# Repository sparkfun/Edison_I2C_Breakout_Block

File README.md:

SparkFun Edison I2C Breakout Block
==================================

[*SparkFun Edison I2C Breakout Block(DEV-13034)*](https://www.sparkfun.com/products/13034)

This I2C Block simply breaks out an I2C bus on the Intel® Edison while level shifting it from 1.8V to your sensors voltage. This a simple board that can snap into your Edison and be used right away.

Repository Contents
-------------------
* **Hardware** - All Eagle diesgn files (.brd, .sch)
* **/Production** - Test bed files and production panel files

License Information
-------------------
The hardware is released under [Creative Commons ShareAlike 4.0 International](https://creativecommons.org/licenses/by-sa/4.0/).
The code is beerware; if you see me (or any other SparkFun employee) at the local, and you've found our code helpful, please buy us a round!

Distributed as-is; no warranty is given.

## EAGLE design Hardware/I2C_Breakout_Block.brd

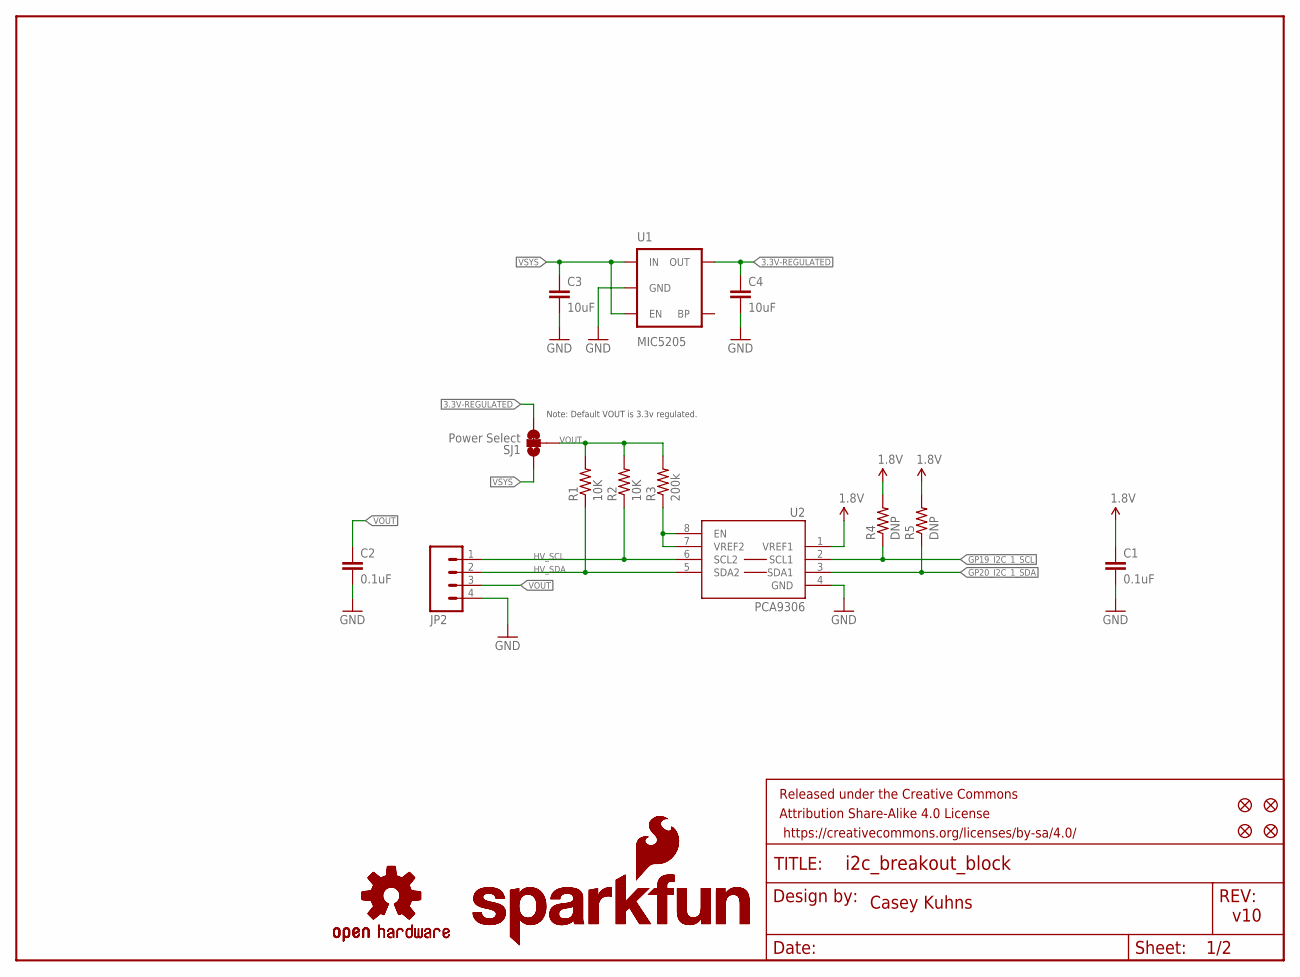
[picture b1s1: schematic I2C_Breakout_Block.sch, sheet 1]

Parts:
C1, C2: 0.1uF; 0603-CAP
C3, C4: 10uF; 1206
FID1, FID2, FID3, FID4: FIDUCIAL1X2; FIDUCIAL-1X2
FRAME1: FRAME-LETTER; CREATIVE_COMMONS
JP2: M04SMD_RA_FEMALE; 1X04_SMD_RA_FEMALE
LOGO1, LOGO3: SFE_LOGO_NAME_FLAME.1_INCH; SFE_LOGO_NAME_FLAME_.1
LOGO2, LOGO4: OSHW-LOGOS; OSHW-LOGO-S
R1, R2: 10K; 0603-RES
R3: 200k; 0603-RES
R4, R5: DNP; 0603-RES
SJ1: Power Select; PAD-JUMPER-3-2OF3_NC_BY_TRACE_YES_SILK_FULL_BOX
U1: MIC5205; SOT23-5
U2: PCA9306; PCA9306DC-1:1

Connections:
1.8V: C1.1, R4.2, R5.2, U2.1 (VREF1); also elsewhere on the board
3.3V-REGULATED: C4.1, SJ1.3, U1.5 (OUT)
GND: C1.2, C2.2, C3.2, C4.2, JP2.4, U1.2 (GND), U2.4 (GND); also elsewhere on the board
GP19_I2C_1_SCL: R4.1, U2.2 (SCL1); also elsewhere on the board
GP20_I2C_1_SDA: R5.1, U2.3 (SDA1); also elsewhere on the board
HV_SCL: JP2.1, R2.1, U2.6 (SCL2)
HV_SDA: JP2.2, R1.1, U2.5 (SDA2)
unnamed: R3.1, U2.7 (VREF2), U2.8 (EN)
VOUT: C2.1, JP2.3, R1.2, R2.2, R3.2, SJ1.2
VSYS: C3.1, SJ1.1, U1.1 (IN), U1.3 (EN); also elsewhere on the board

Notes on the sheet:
Casey Kuhns
v10
Note: Default VOUT is 3.3v regulated.

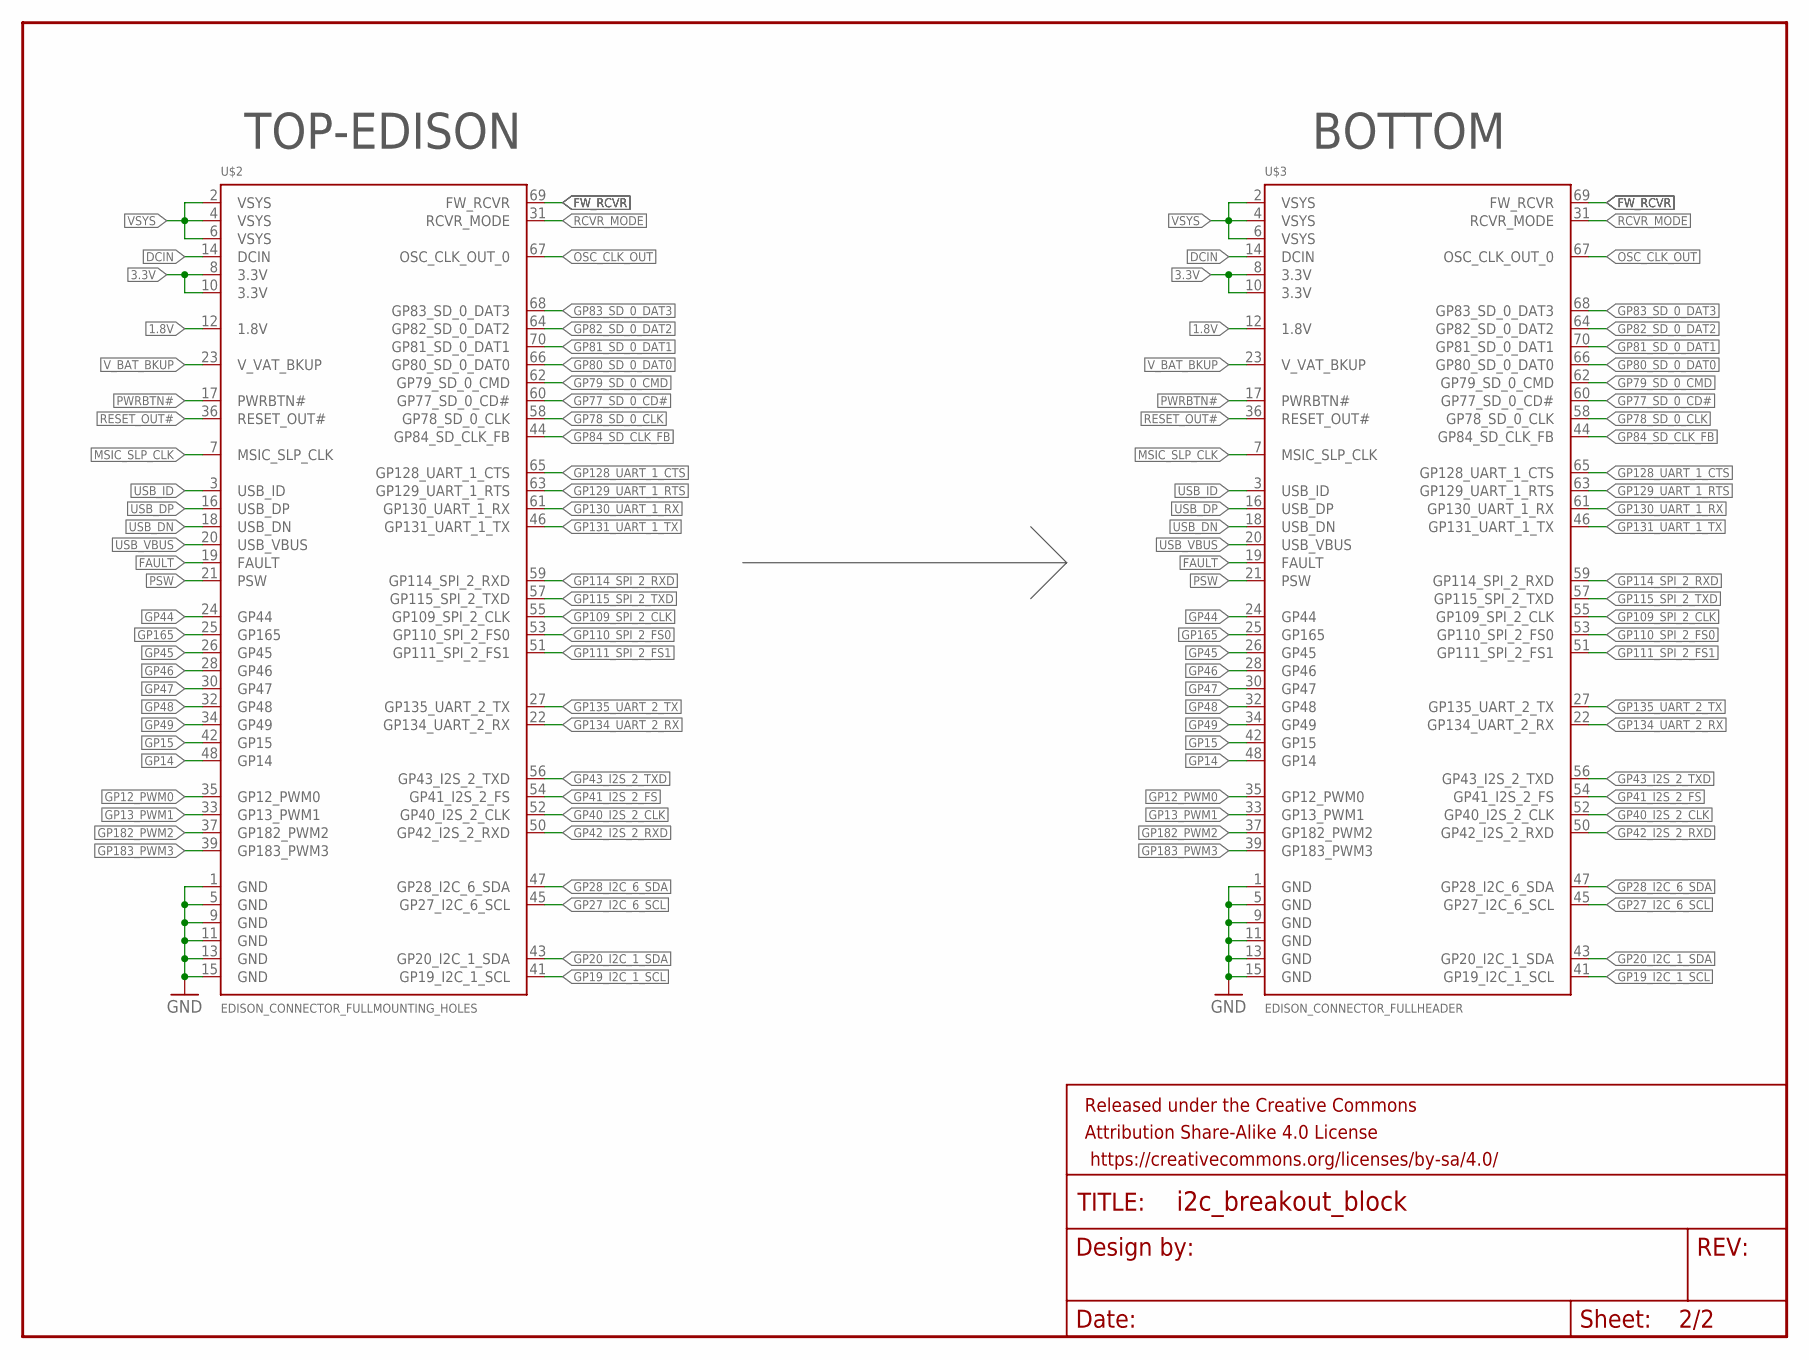
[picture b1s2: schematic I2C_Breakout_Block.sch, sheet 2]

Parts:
FRAME2: FRAME-LETTER; CREATIVE_COMMONS
U$2: EDISON_CONNECTOR_FULLMOUNTING_HOLES; EDISON_DAUGHTER
U$3: EDISON_CONNECTOR_FULLHEADER; DF40C-70DP-0.4(51)

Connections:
1.8V: U$2.12 (1.8V), U$3.12 (1.8V); also elsewhere on the board
3.3V: U$2.8 (3.3V), U$2.10 (3.3V), U$3.8 (3.3V), U$3.10 (3.3V)
DCIN: U$2.14 (DCIN), U$3.14 (DCIN)
FAULT: U$2.19 (FAULT), U$3.19 (FAULT)
FW_RCVR: U$2.69 (FW_RCVR), U$3.69 (FW_RCVR)
GND: U$2.1 (GND), U$2.5 (GND), U$2.9 (GND), U$2.11 (GND), U$2.13 (GND), U$2.15 (GND), U$3.1 (GND), U$3.5 (GND), U$3.9 (GND), U$3.11 (GND), U$3.13 (GND), U$3.15 (GND); also elsewhere on the board
GP12_PWM0: U$2.35 (GP12_PWM0), U$3.35 (GP12_PWM0)
GP13_PWM1: U$2.33 (GP13_PWM1), U$3.33 (GP13_PWM1)
GP14: U$2.48 (GP14), U$3.48 (GP14)
GP15: U$2.42 (GP15), U$3.42 (GP15)
GP19_I2C_1_SCL: U$2.41 (GP19_I2C_1_SCL), U$3.41 (GP19_I2C_1_SCL); also elsewhere on the board
GP20_I2C_1_SDA: U$2.43 (GP20_I2C_1_SDA), U$3.43 (GP20_I2C_1_SDA); also elsewhere on the board
GP27_I2C_6_SCL: U$2.45 (GP27_I2C_6_SCL), U$3.45 (GP27_I2C_6_SCL)
GP28_I2C_6_SDA: U$2.47 (GP28_I2C_6_SDA), U$3.47 (GP28_I2C_6_SDA)
GP40_I2S_2_CLK: U$2.52 (GP40_I2S_2_CLK), U$3.52 (GP40_I2S_2_CLK)
GP41_I2S_2_FS: U$2.54 (GP41_I2S_2_FS), U$3.54 (GP41_I2S_2_FS)
GP42_I2S_2_RXD: U$2.50 (GP42_I2S_2_RXD), U$3.50 (GP42_I2S_2_RXD)
GP43_I2S_2_TXD: U$2.56 (GP43_I2S_2_TXD), U$3.56 (GP43_I2S_2_TXD)
GP44: U$2.24 (GP44), U$3.24 (GP44)
GP45: U$2.26 (GP45), U$3.26 (GP45)
GP46: U$2.28 (GP46), U$3.28 (GP46)
GP47: U$2.30 (GP47), U$3.30 (GP47)
GP48: U$2.32 (GP48), U$3.32 (GP48)
GP49: U$2.34 (GP49), U$3.34 (GP49)
GP77_SD_0_CD#: U$2.60 (GP77_SD_0_CD#), U$3.60 (GP77_SD_0_CD#)
GP78_SD_0_CLK: U$2.58 (GP78_SD_0_CLK), U$3.58 (GP78_SD_0_CLK)
GP79_SD_0_CMD: U$2.62 (GP79_SD_0_CMD), U$3.62 (GP79_SD_0_CMD)
GP80_SD_0_DAT0: U$2.66 (GP80_SD_0_DAT0), U$3.66 (GP80_SD_0_DAT0)
GP81_SD_0_DAT1: U$2.70 (GP81_SD_0_DAT1), U$3.70 (GP81_SD_0_DAT1)
GP82_SD_0_DAT2: U$2.64 (GP82_SD_0_DAT2), U$3.64 (GP82_SD_0_DAT2)
GP83_SD_0_DAT3: U$2.68 (GP83_SD_0_DAT3), U$3.68 (GP83_SD_0_DAT3)
GP84_SD_CLK_FB: U$2.44 (GP84_SD_CLK_FB), U$3.44 (GP84_SD_CLK_FB)
GP109_SPI_2_CLK: U$2.55 (GP109_SPI_2_CLK), U$3.55 (GP109_SPI_2_CLK)
GP110_SPI_2_FS0: U$2.53 (GP110_SPI_2_FS0), U$3.53 (GP110_SPI_2_FS0)
GP111_SPI_2_FS1: U$2.51 (GP111_SPI_2_FS1), U$3.51 (GP111_SPI_2_FS1)
GP114_SPI_2_RXD: U$2.59 (GP114_SPI_2_RXD), U$3.59 (GP114_SPI_2_RXD)
GP115_SPI_2_TXD: U$2.57 (GP115_SPI_2_TXD), U$3.57 (GP115_SPI_2_TXD)
GP128_UART_1_CTS: U$2.65 (GP128_UART_1_CTS), U$3.65 (GP128_UART_1_CTS)
GP129_UART_1_RTS: U$2.63 (GP129_UART_1_RTS), U$3.63 (GP129_UART_1_RTS)
GP130_UART_1_RX: U$2.61 (GP130_UART_1_RX), U$3.61 (GP130_UART_1_RX)
GP131_UART_1_TX: U$2.46 (GP131_UART_1_TX), U$3.46 (GP131_UART_1_TX)
GP134_UART_2_RX: U$2.22 (GP134_UART_2_RX), U$3.22 (GP134_UART_2_RX)
GP135_UART_2_TX: U$2.27 (GP135_UART_2_TX), U$3.27 (GP135_UART_2_TX)
GP165: U$2.25 (GP165), U$3.25 (GP165)
GP182_PWM2: U$2.37 (GP182_PWM2), U$3.37 (GP182_PWM2)
GP183_PWM3: U$2.39 (GP183_PWM3), U$3.39 (GP183_PWM3)
MSIC_SLP_CLK: U$2.7 (MSIC_SLP_CLK), U$3.7 (MSIC_SLP_CLK)
OSC_CLK_OUT: U$2.67 (OSC_CLK_OUT_0), U$3.67 (OSC_CLK_OUT_0)
PSW: U$2.21 (PSW), U$3.21 (PSW)
PWRBTN#: U$2.17 (PWRBTN#), U$3.17 (PWRBTN#)
RCVR_MODE: U$2.31 (RCVR_MODE), U$3.31 (RCVR_MODE)
RESET_OUT#: U$2.36 (RESET_OUT#), U$3.36 (RESET_OUT#)
USB_DN: U$2.18 (USB_DN), U$3.18 (USB_DN)
USB_DP: U$2.16 (USB_DP), U$3.16 (USB_DP)
USB_ID: U$2.3 (USB_ID), U$3.3 (USB_ID)
USB_VBUS: U$2.20 (USB_VBUS), U$3.20 (USB_VBUS)
VSYS: U$2.2 (VSYS), U$2.4 (VSYS), U$2.6 (VSYS), U$3.2 (VSYS), U$3.4 (VSYS), U$3.6 (VSYS); also elsewhere on the board
V_BAT_BKUP: U$2.23 (V_VAT_BKUP), U$3.23 (V_VAT_BKUP)

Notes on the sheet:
TOP-EDISON
BOTTOM

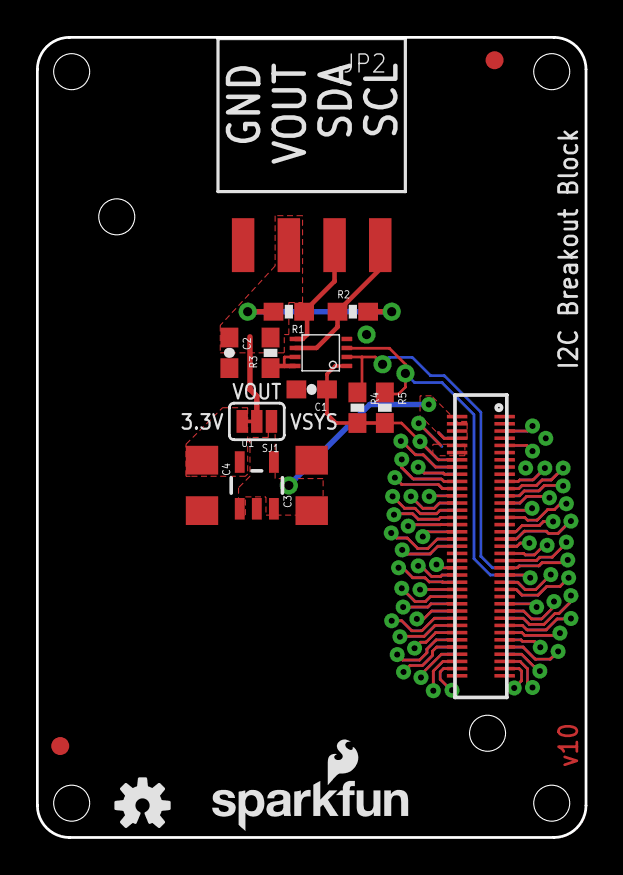
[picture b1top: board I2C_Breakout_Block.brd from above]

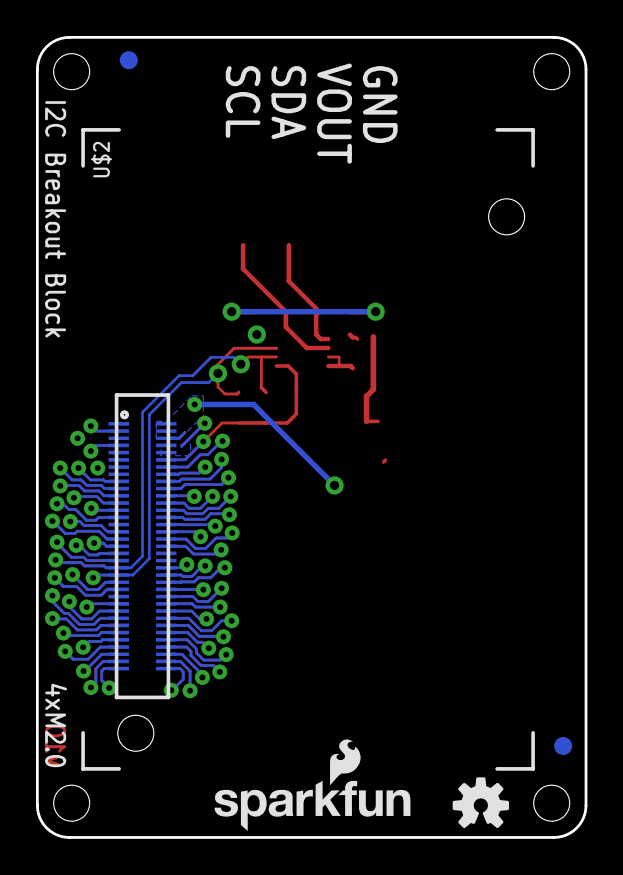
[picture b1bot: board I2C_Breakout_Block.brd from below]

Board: 2 copper layers, 30.5 x 44.5 mm, 25 parts (6 on the bottom side), 63 nets.

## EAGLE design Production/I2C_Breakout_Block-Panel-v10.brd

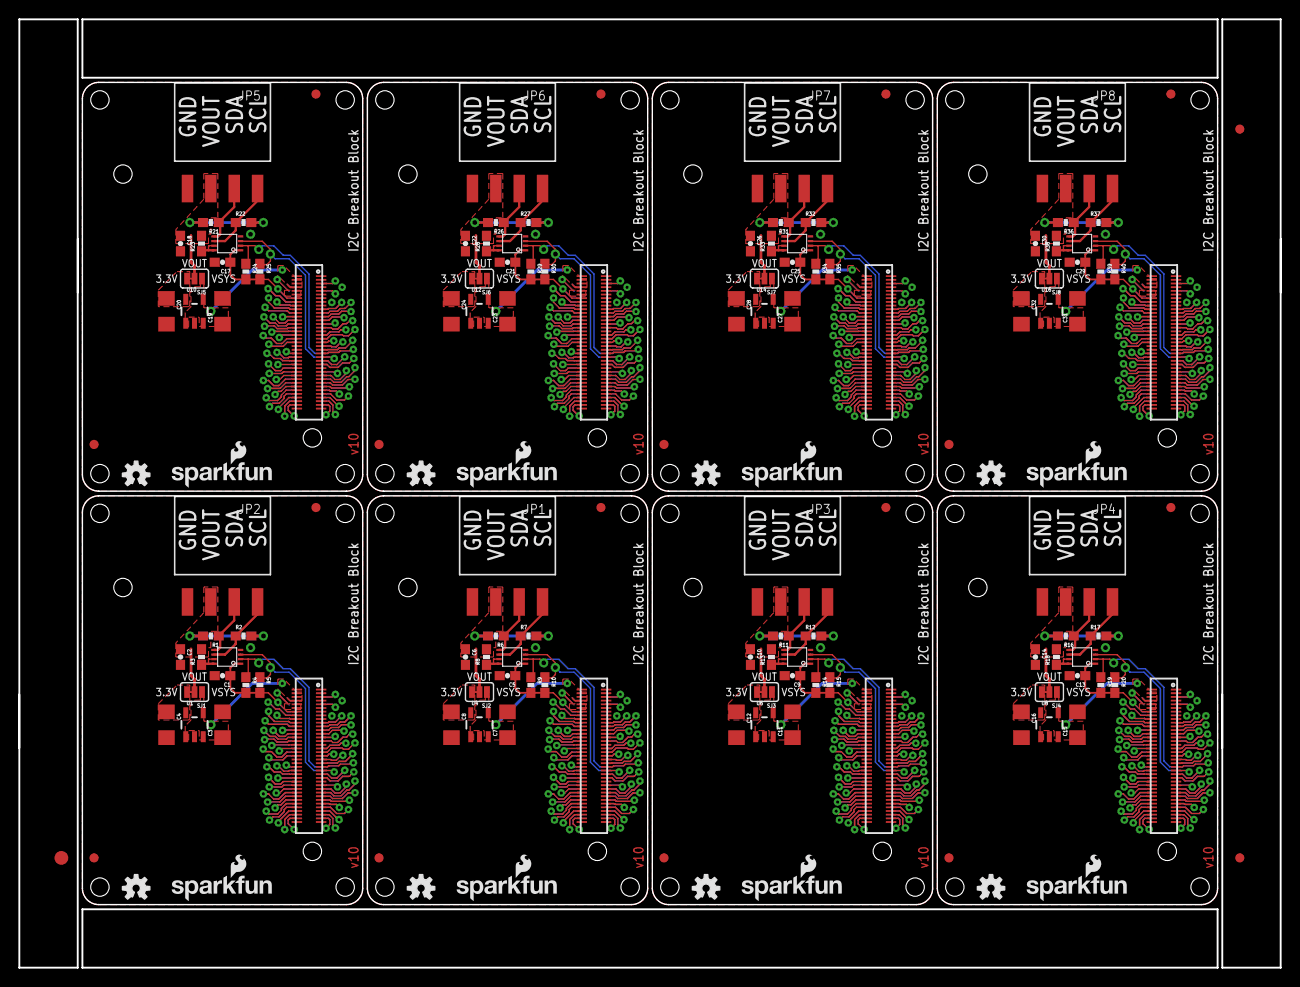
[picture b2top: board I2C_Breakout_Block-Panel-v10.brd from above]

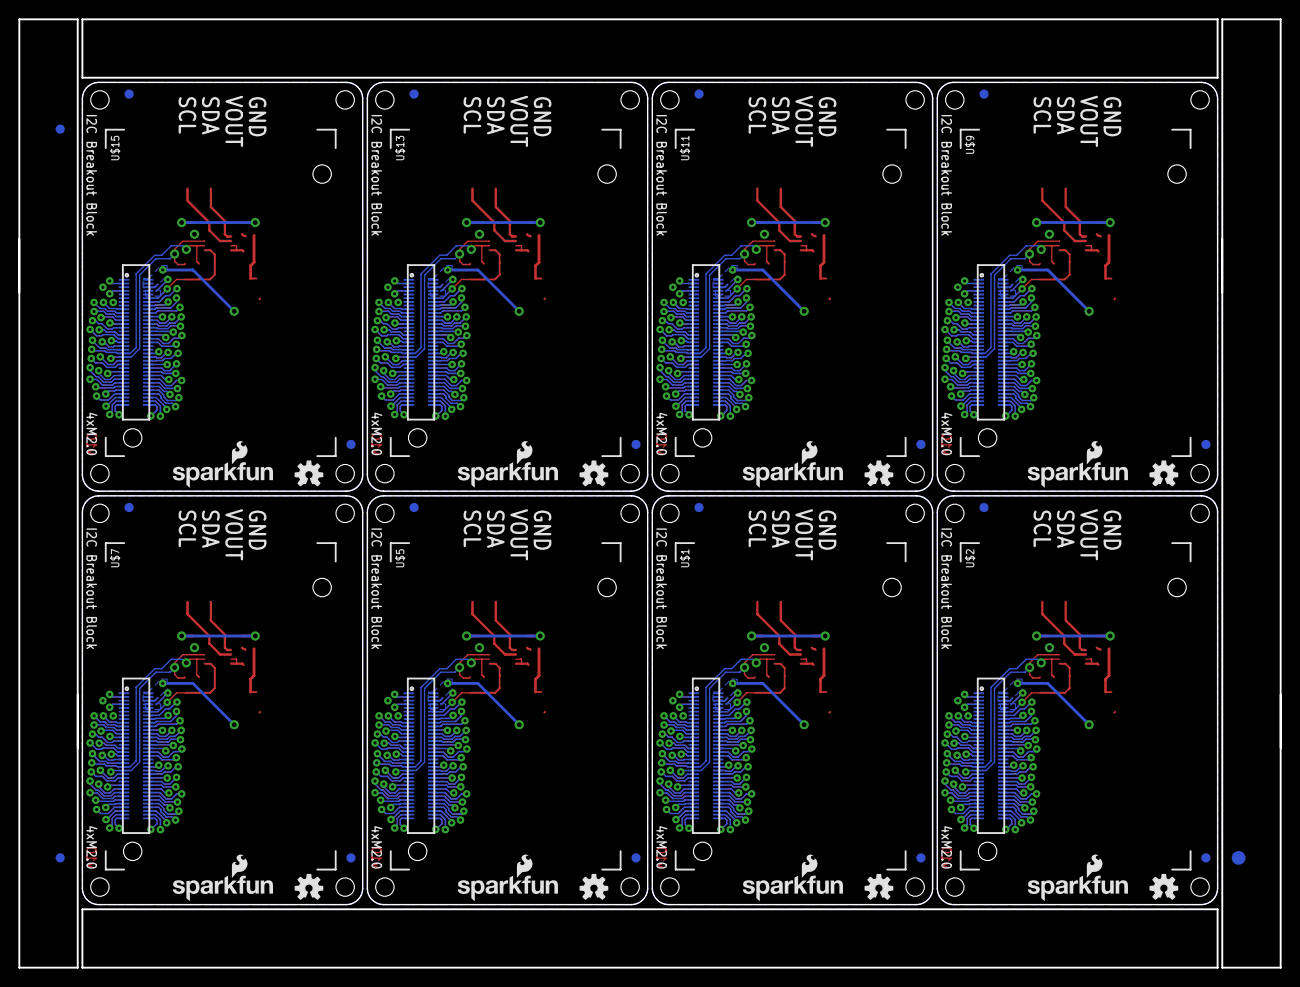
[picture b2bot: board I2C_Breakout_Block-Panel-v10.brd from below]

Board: 2 copper layers, 137.2 x 103.1 mm, 190 parts (51 on the bottom side), 504 nets.

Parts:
C1, C2, C5, C6, C9, C10, C13, C14, C17, C18, C21, C22, C25, C26, C29, C30: 0.1uF; 0603-CAP
C3, C4, C7, C8, C11, C12, C15, C16, C19, C20, C23, C24, C27, C28, C31, C32: 10uF; 1206
E$1, E$2: FIDUCIAL-1.5X3
E$3, E$4, E$5, E$6: FIDUCIAL-1X2
FID1, FID2, FID3, FID4, FID5, FID6, FID7, FID8, FID9, FID10, FID11, FID12, FID13, FID14, FID15, FID16, FID17, FID18, FID19, FID20, FID21, FID22, FID23, FID24, FID25, FID26, FID27, FID28, FID29, FID30, FID31, FID32: FIDUCIAL1X2; FIDUCIAL-1X2
JP1, JP2, JP3, JP4, JP5, JP6, JP7, JP8: 1X04_SMD_RA_FEMALE
LOGO1, LOGO3, LOGO6, LOGO7, LOGO10, LOGO11, LOGO14, LOGO15, LOGO18, LOGO19, LOGO22, LOGO23, LOGO26, LOGO27, LOGO30, LOGO31: SFE_LOGO_NAME_FLAME.1_INCH; SFE_LOGO_NAME_FLAME_.1
LOGO2, LOGO4, LOGO5, LOGO8, LOGO9, LOGO12, LOGO13, LOGO16, LOGO17, LOGO20, LOGO21, LOGO24, LOGO25, LOGO28, LOGO29, LOGO32: OSHW-LOGOS; OSHW-LOGO-S
R1, R2, R6, R7, R11, R12, R16, R17, R21, R22, R26, R27, R31, R32, R36, R37: 10K; 0603-RES
R3, R8, R13, R18, R23, R28, R33, R38: 200k; 0603-RES
R4, R5, R9, R10, R14, R15, R19, R20, R24, R25, R29, R30, R34, R35, R39, R40: DNP; 0603-RES
SJ1, SJ2, SJ3, SJ4, SJ5, SJ6, SJ7, SJ8: Power Select; PAD-JUMPER-3-2OF3_NC_BY_TRACE_YES_SILK_FULL_BOX
U1, U4, U6, U8, U10, U12, U14, U16: MIC5205; SOT23-5
U2, U3, U5, U7, U9, U11, U13, U15: PCA9306; PCA9306DC-1:1
U$1, U$2, U$5, U$7, U$9, U$11, U$13, U$15: EDISON_CONNECTOR_FULLMOUNTING_HOLES; EDISON_DAUGHTER
U$3, U$4, U$6, U$8, U$10, U$12, U$14, U$16: EDISON_CONNECTOR_FULLHEADER; DF40C-70DP-0.4(51)

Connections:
1.8V: C1.1, R4.2, R5.2, U2.1, U$2.12, U$3.12
1.8V1: C5.1, R9.2, R10.2, U3.1, U$1.12, U$4.12
1.8V2: C9.1, R14.2, R15.2, U5.1, U$5.12, U$6.12
1.8V3: C13.1, R19.2, R20.2, U7.1, U$7.12, U$8.12
1.8V4: C17.1, R24.2, R25.2, U9.1, U$9.12, U$10.12
1.8V5: C21.1, R29.2, R30.2, U11.1, U$11.12, U$12.12
1.8V6: C25.1, R34.2, R35.2, U13.1, U$13.12, U$14.12
1.8V7: C29.1, R39.2, R40.2, U15.1, U$15.12, U$16.12
3.3V: U$2.8, U$2.10, U$3.8, U$3.10
3.3V1: U$1.8, U$1.10, U$4.8, U$4.10
3.3V2: U$5.8, U$5.10, U$6.8, U$6.10
3.3V3: U$7.8, U$7.10, U$8.8, U$8.10
3.3V4: U$9.8, U$9.10, U$10.8, U$10.10
3.3V5: U$11.8, U$11.10, U$12.8, U$12.10
3.3V6: U$13.8, U$13.10, U$14.8, U$14.10
3.3V7: U$15.8, U$15.10, U$16.8, U$16.10
3.3V-REGULATED: C4.1, SJ1.3, U1.5
3.3V-REGULATED1: C8.1, SJ2.3, U4.5
3.3V-REGULATED2: C12.1, SJ3.3, U6.5
3.3V-REGULATED3: C16.1, SJ4.3, U8.5
3.3V-REGULATED4: C20.1, SJ5.3, U10.5
3.3V-REGULATED5: C24.1, SJ6.3, U12.5
3.3V-REGULATED6: C28.1, SJ7.3, U14.5
3.3V-REGULATED7: C32.1, SJ8.3, U16.5
DCIN: U$2.14, U$3.14
DCIN1: U$1.14, U$4.14
DCIN2: U$5.14, U$6.14
DCIN3: U$7.14, U$8.14
DCIN4: U$9.14, U$10.14
DCIN5: U$11.14, U$12.14
DCIN6: U$13.14, U$14.14
DCIN7: U$15.14, U$16.14
FAULT: U$2.19, U$3.19
FAULT1: U$1.19, U$4.19
FAULT2: U$5.19, U$6.19
FAULT3: U$7.19, U$8.19
FAULT4: U$9.19, U$10.19
FAULT5: U$11.19, U$12.19
FAULT6: U$13.19, U$14.19
FAULT7: U$15.19, U$16.19
FW_RCVR: U$2.69, U$3.69
FW_RCVR1: U$1.69, U$4.69
FW_RCVR2: U$5.69, U$6.69
FW_RCVR3: U$7.69, U$8.69
FW_RCVR4: U$9.69, U$10.69
FW_RCVR5: U$11.69, U$12.69
FW_RCVR6: U$13.69, U$14.69
FW_RCVR7: U$15.69, U$16.69
GND: C1.2, C2.2, C3.2, C4.2, JP2.4, U1.2, U2.4, U$2.1, U$2.5, U$2.9, U$2.11, U$2.13, U$2.15, U$3.1, U$3.5, U$3.9, U$3.11, U$3.13, U$3.15
GND1: C5.2, C6.2, C7.2, C8.2, JP1.4, U3.4, U4.2, U$1.1, U$1.5, U$1.9, U$1.11, U$1.13, U$1.15, U$4.1, U$4.5, U$4.9, U$4.11, U$4.13, U$4.15
GND2: C9.2, C10.2, C11.2, C12.2, JP3.4, U5.4, U6.2, U$5.1, U$5.5, U$5.9, U$5.11, U$5.13, U$5.15, U$6.1, U$6.5, U$6.9, U$6.11, U$6.13, U$6.15
GND3: C13.2, C14.2, C15.2, C16.2, JP4.4, U7.4, U8.2, U$7.1, U$7.5, U$7.9, U$7.11, U$7.13, U$7.15, U$8.1, U$8.5, U$8.9, U$8.11, U$8.13, U$8.15
GND4: C17.2, C18.2, C19.2, C20.2, JP5.4, U9.4, U10.2, U$9.1, U$9.5, U$9.9, U$9.11, U$9.13, U$9.15, U$10.1, U$10.5, U$10.9, U$10.11, U$10.13, U$10.15
GND5: C21.2, C22.2, C23.2, C24.2, JP6.4, U11.4, U12.2, U$11.1, U$11.5, U$11.9, U$11.11, U$11.13, U$11.15, U$12.1, U$12.5, U$12.9, U$12.11, U$12.13, U$12.15
GND6: C25.2, C26.2, C27.2, C28.2, JP7.4, U13.4, U14.2, U$13.1, U$13.5, U$13.9, U$13.11, U$13.13, U$13.15, U$14.1, U$14.5, U$14.9, U$14.11, U$14.13, U$14.15
GND7: C29.2, C30.2, C31.2, C32.2, JP8.4, U15.4, U16.2, U$15.1, U$15.5, U$15.9, U$15.11, U$15.13, U$15.15, U$16.1, U$16.5, U$16.9, U$16.11, U$16.13, U$16.15
GP1: U$1.48, U$4.48
GP2: U$1.42, U$4.42
GP3: U$1.34, U$4.34
GP4: U$1.32, U$4.32
GP5: U$1.30, U$4.30
GP6: U$1.28, U$4.28
GP7: U$1.26, U$4.26
GP8: U$1.25, U$4.25
GP9: U$1.24, U$4.24
GP10: U$5.48, U$6.48
GP11: U$5.42, U$6.42
GP12: U$5.34, U$6.34
GP12_PWM0: U$2.35, U$3.35
GP12_PWM1: U$1.35, U$4.35
GP12_PWM2: U$5.35, U$6.35
GP12_PWM3: U$7.35, U$8.35
GP12_PWM4: U$9.35, U$10.35
GP12_PWM5: U$11.35, U$12.35
GP12_PWM6: U$13.35, U$14.35
GP12_PWM7: U$15.35, U$16.35
GP13: U$5.32, U$6.32
GP13_PWM1: U$2.33, U$3.33
GP13_PWM2: U$1.33, U$4.33
GP13_PWM3: U$5.33, U$6.33
GP13_PWM4: U$7.33, U$8.33
GP13_PWM5: U$9.33, U$10.33
GP13_PWM6: U$11.33, U$12.33
GP13_PWM7: U$13.33, U$14.33
GP13_PWM8: U$15.33, U$16.33
GP14: U$2.48, U$3.48
GP15: U$2.42, U$3.42
GP16: U$5.30, U$6.30
GP17: U$5.28, U$6.28
GP18: U$5.26, U$6.26
GP19: U$5.25, U$6.25
GP19_I2C_1_SCL: R4.1, U2.2, U$2.41, U$3.41
GP19_I2C_1_SCL1: R9.1, U3.2, U$1.41, U$4.41
GP19_I2C_1_SCL2: R14.1, U5.2, U$5.41, U$6.41
GP19_I2C_1_SCL3: R19.1, U7.2, U$7.41, U$8.41
GP19_I2C_1_SCL4: R24.1, U9.2, U$9.41, U$10.41
GP19_I2C_1_SCL5: R29.1, U11.2, U$11.41, U$12.41
GP19_I2C_1_SCL6: R34.1, U13.2, U$13.41, U$14.41
GP19_I2C_1_SCL7: R39.1, U15.2, U$15.41, U$16.41
GP20: U$5.24, U$6.24
GP20_I2C_1_SDA: R5.1, U2.3, U$2.43, U$3.43
GP20_I2C_1_SDA1: R10.1, U3.3, U$1.43, U$4.43
GP20_I2C_1_SDA2: R15.1, U5.3, U$5.43, U$6.43
GP20_I2C_1_SDA3: R20.1, U7.3, U$7.43, U$8.43
GP20_I2C_1_SDA4: R25.1, U9.3, U$9.43, U$10.43
GP20_I2C_1_SDA5: R30.1, U11.3, U$11.43, U$12.43
GP20_I2C_1_SDA6: R35.1, U13.3, U$13.43, U$14.43
GP20_I2C_1_SDA7: R40.1, U15.3, U$15.43, U$16.43
GP21: U$7.48, U$8.48
GP22: U$7.42, U$8.42
GP23: U$7.34, U$8.34
GP24: U$7.32, U$8.32
GP25: U$7.30, U$8.30
GP26: U$7.28, U$8.28
GP27: U$7.26, U$8.26
GP27_I2C_6_SCL: U$2.45, U$3.45
GP27_I2C_6_SCL1: U$1.45, U$4.45
GP27_I2C_6_SCL2: U$5.45, U$6.45
GP27_I2C_6_SCL3: U$7.45, U$8.45
GP27_I2C_6_SCL4: U$9.45, U$10.45
GP27_I2C_6_SCL5: U$11.45, U$12.45
GP27_I2C_6_SCL6: U$13.45, U$14.45
GP27_I2C_6_SCL7: U$15.45, U$16.45
GP28: U$7.25, U$8.25
GP28_I2C_6_SDA: U$2.47, U$3.47
GP28_I2C_6_SDA1: U$1.47, U$4.47
GP28_I2C_6_SDA2: U$5.47, U$6.47
GP28_I2C_6_SDA3: U$7.47, U$8.47
GP28_I2C_6_SDA4: U$9.47, U$10.47
GP28_I2C_6_SDA5: U$11.47, U$12.47
GP28_I2C_6_SDA6: U$13.47, U$14.47
GP28_I2C_6_SDA7: U$15.47, U$16.47
GP29: U$7.24, U$8.24
GP30: U$9.48, U$10.48
GP31: U$9.42, U$10.42
GP32: U$9.34, U$10.34
GP33: U$9.32, U$10.32
GP34: U$9.30, U$10.30
GP35: U$9.28, U$10.28
GP36: U$9.26, U$10.26
GP37: U$9.25, U$10.25
GP38: U$9.24, U$10.24
GP39: U$11.48, U$12.48
GP40: U$11.42, U$12.42
GP40_I2S_2_CLK: U$2.52, U$3.52
GP40_I2S_2_CLK1: U$1.52, U$4.52
GP40_I2S_2_CLK2: U$5.52, U$6.52
GP40_I2S_2_CLK3: U$7.52, U$8.52
GP40_I2S_2_CLK4: U$9.52, U$10.52
GP40_I2S_2_CLK5: U$11.52, U$12.52
GP40_I2S_2_CLK6: U$13.52, U$14.52
GP40_I2S_2_CLK7: U$15.52, U$16.52
GP41: U$11.34, U$12.34
GP41_I2S_2_FS: U$2.54, U$3.54
GP41_I2S_2_FS1: U$1.54, U$4.54
GP41_I2S_2_FS2: U$5.54, U$6.54
GP41_I2S_2_FS3: U$7.54, U$8.54
GP41_I2S_2_FS4: U$9.54, U$10.54
GP41_I2S_2_FS5: U$11.54, U$12.54
GP41_I2S_2_FS6: U$13.54, U$14.54
GP41_I2S_2_FS7: U$15.54, U$16.54
GP42: U$11.32, U$12.32
GP42_I2S_2_RXD: U$2.50, U$3.50
GP42_I2S_2_RXD1: U$1.50, U$4.50
GP42_I2S_2_RXD2: U$5.50, U$6.50
GP42_I2S_2_RXD3: U$7.50, U$8.50
GP42_I2S_2_RXD4: U$9.50, U$10.50
GP42_I2S_2_RXD5: U$11.50, U$12.50
GP42_I2S_2_RXD6: U$13.50, U$14.50
GP42_I2S_2_RXD7: U$15.50, U$16.50
GP43: U$11.30, U$12.30
GP43_I2S_2_TXD: U$2.56, U$3.56
GP43_I2S_2_TXD1: U$1.56, U$4.56
GP43_I2S_2_TXD2: U$5.56, U$6.56
GP43_I2S_2_TXD3: U$7.56, U$8.56
GP43_I2S_2_TXD4: U$9.56, U$10.56
GP43_I2S_2_TXD5: U$11.56, U$12.56
GP43_I2S_2_TXD6: U$13.56, U$14.56
GP43_I2S_2_TXD7: U$15.56, U$16.56
GP44: U$2.24, U$3.24
GP45: U$2.26, U$3.26
GP46: U$2.28, U$3.28
GP47: U$2.30, U$3.30
GP48: U$2.32, U$3.32
GP49: U$2.34, U$3.34
GP50: U$11.28, U$12.28
GP51: U$11.26, U$12.26
GP52: U$11.25, U$12.25
GP53: U$11.24, U$12.24
GP54: U$13.48, U$14.48
GP55: U$13.42, U$14.42
GP56: U$13.34, U$14.34
GP57: U$13.32, U$14.32
GP58: U$13.30, U$14.30
GP59: U$13.28, U$14.28
GP60: U$13.26, U$14.26
GP61: U$13.25, U$14.25
GP62: U$13.24, U$14.24
GP63: U$15.48, U$16.48
GP64: U$15.42, U$16.42
GP65: U$15.34, U$16.34
GP66: U$15.32, U$16.32
GP67: U$15.30, U$16.30
GP68: U$15.28, U$16.28
GP69: U$15.26, U$16.26
GP70: U$15.25, U$16.25
GP71: U$15.24, U$16.24
GP77_SD_0_CD#: U$2.60, U$3.60
GP77_SD_0_CD#1: U$1.60, U$4.60
GP77_SD_0_CD#2: U$5.60, U$6.60
GP77_SD_0_CD#3: U$7.60, U$8.60
GP77_SD_0_CD#4: U$9.60, U$10.60
GP77_SD_0_CD#5: U$11.60, U$12.60
GP77_SD_0_CD#6: U$13.60, U$14.60
GP77_SD_0_CD#7: U$15.60, U$16.60
GP78_SD_0_CLK: U$2.58, U$3.58
GP78_SD_0_CLK1: U$1.58, U$4.58
GP78_SD_0_CLK2: U$5.58, U$6.58
GP78_SD_0_CLK3: U$7.58, U$8.58
GP78_SD_0_CLK4: U$9.58, U$10.58
GP78_SD_0_CLK5: U$11.58, U$12.58
GP78_SD_0_CLK6: U$13.58, U$14.58
GP78_SD_0_CLK7: U$15.58, U$16.58
GP79_SD_0_CMD: U$2.62, U$3.62
GP79_SD_0_CMD1: U$1.62, U$4.62
GP79_SD_0_CMD2: U$5.62, U$6.62
GP79_SD_0_CMD3: U$7.62, U$8.62
GP79_SD_0_CMD4: U$9.62, U$10.62
GP79_SD_0_CMD5: U$11.62, U$12.62
GP79_SD_0_CMD6: U$13.62, U$14.62
GP79_SD_0_CMD7: U$15.62, U$16.62
GP80_SD_0_DAT0: U$2.66, U$3.66
GP80_SD_0_DAT1: U$1.66, U$4.66
GP80_SD_0_DAT2: U$5.66, U$6.66
GP80_SD_0_DAT3: U$7.66, U$8.66
GP80_SD_0_DAT4: U$9.66, U$10.66
GP80_SD_0_DAT5: U$11.66, U$12.66
GP80_SD_0_DAT6: U$13.66, U$14.66
GP80_SD_0_DAT7: U$15.66, U$16.66
GP81_SD_0_DAT1: U$2.70, U$3.70
GP81_SD_0_DAT2: U$1.70, U$4.70
GP81_SD_0_DAT3: U$5.70, U$6.70
GP81_SD_0_DAT4: U$7.70, U$8.70
GP81_SD_0_DAT5: U$9.70, U$10.70
GP81_SD_0_DAT6: U$11.70, U$12.70
GP81_SD_0_DAT7: U$13.70, U$14.70
GP81_SD_0_DAT8: U$15.70, U$16.70
GP82_SD_0_DAT1: U$1.64, U$4.64
GP82_SD_0_DAT2: U$2.64, U$3.64
GP82_SD_0_DAT3: U$5.64, U$6.64
GP82_SD_0_DAT4: U$7.64, U$8.64
GP82_SD_0_DAT5: U$9.64, U$10.64
GP82_SD_0_DAT6: U$11.64, U$12.64
GP82_SD_0_DAT7: U$13.64, U$14.64
GP82_SD_0_DAT8: U$15.64, U$16.64
GP83_SD_0_DAT1: U$1.68, U$4.68
GP83_SD_0_DAT2: U$5.68, U$6.68
GP83_SD_0_DAT3: U$2.68, U$3.68
GP83_SD_0_DAT4: U$7.68, U$8.68
GP83_SD_0_DAT5: U$9.68, U$10.68
GP83_SD_0_DAT6: U$11.68, U$12.68
GP83_SD_0_DAT7: U$13.68, U$14.68
GP83_SD_0_DAT8: U$15.68, U$16.68
GP84_SD_CLK_FB: U$2.44, U$3.44
GP84_SD_CLK_FB1: U$1.44, U$4.44
GP84_SD_CLK_FB2: U$5.44, U$6.44
GP84_SD_CLK_FB3: U$7.44, U$8.44
GP84_SD_CLK_FB4: U$9.44, U$10.44
GP84_SD_CLK_FB5: U$11.44, U$12.44
GP84_SD_CLK_FB6: U$13.44, U$14.44
GP84_SD_CLK_FB7: U$15.44, U$16.44
GP109_SPI_2_CLK: U$2.55, U$3.55
GP109_SPI_2_CLK1: U$1.55, U$4.55
GP109_SPI_2_CLK2: U$5.55, U$6.55
GP109_SPI_2_CLK3: U$7.55, U$8.55
GP109_SPI_2_CLK4: U$9.55, U$10.55
GP109_SPI_2_CLK5: U$11.55, U$12.55
GP109_SPI_2_CLK6: U$13.55, U$14.55
GP109_SPI_2_CLK7: U$15.55, U$16.55
GP110_SPI_2_FS0: U$2.53, U$3.53
GP110_SPI_2_FS1: U$1.53, U$4.53
GP110_SPI_2_FS2: U$5.53, U$6.53
GP110_SPI_2_FS3: U$7.53, U$8.53
GP110_SPI_2_FS4: U$9.53, U$10.53
GP110_SPI_2_FS5: U$11.53, U$12.53
GP110_SPI_2_FS6: U$13.53, U$14.53
GP110_SPI_2_FS7: U$15.53, U$16.53
GP111_SPI_2_FS1: U$2.51, U$3.51
GP111_SPI_2_FS2: U$1.51, U$4.51
GP111_SPI_2_FS3: U$5.51, U$6.51
GP111_SPI_2_FS4: U$7.51, U$8.51
GP111_SPI_2_FS5: U$9.51, U$10.51
GP111_SPI_2_FS6: U$11.51, U$12.51
GP111_SPI_2_FS7: U$13.51, U$14.51
GP111_SPI_2_FS8: U$15.51, U$16.51
GP114_SPI_2_RXD: U$2.59, U$3.59
GP114_SPI_2_RXD1: U$1.59, U$4.59
GP114_SPI_2_RXD2: U$5.59, U$6.59
GP114_SPI_2_RXD3: U$7.59, U$8.59
GP114_SPI_2_RXD4: U$9.59, U$10.59
GP114_SPI_2_RXD5: U$11.59, U$12.59
GP114_SPI_2_RXD6: U$13.59, U$14.59
GP114_SPI_2_RXD7: U$15.59, U$16.59
GP115_SPI_2_TXD: U$2.57, U$3.57
GP115_SPI_2_TXD1: U$1.57, U$4.57
GP115_SPI_2_TXD2: U$5.57, U$6.57
GP115_SPI_2_TXD3: U$7.57, U$8.57
GP115_SPI_2_TXD4: U$9.57, U$10.57
GP115_SPI_2_TXD5: U$11.57, U$12.57
GP115_SPI_2_TXD6: U$13.57, U$14.57
GP115_SPI_2_TXD7: U$15.57, U$16.57
GP128_UART_1_CTS: U$2.65, U$3.65
GP128_UART_1_CTS1: U$1.65, U$4.65
GP128_UART_1_CTS2: U$5.65, U$6.65
GP128_UART_1_CTS3: U$7.65, U$8.65
GP128_UART_1_CTS4: U$9.65, U$10.65
GP128_UART_1_CTS5: U$11.65, U$12.65
GP128_UART_1_CTS6: U$13.65, U$14.65
GP128_UART_1_CTS7: U$15.65, U$16.65
GP129_UART_1_RTS: U$2.63, U$3.63
GP129_UART_1_RTS1: U$1.63, U$4.63
GP129_UART_1_RTS2: U$5.63, U$6.63
GP129_UART_1_RTS3: U$7.63, U$8.63
GP129_UART_1_RTS4: U$9.63, U$10.63
GP129_UART_1_RTS5: U$11.63, U$12.63
GP129_UART_1_RTS6: U$13.63, U$14.63
GP129_UART_1_RTS7: U$15.63, U$16.63
GP130_UART_1_RX: U$2.61, U$3.61
GP130_UART_1_RX1: U$1.61, U$4.61
GP130_UART_1_RX2: U$5.61, U$6.61
GP130_UART_1_RX3: U$7.61, U$8.61
GP130_UART_1_RX4: U$9.61, U$10.61
GP130_UART_1_RX5: U$11.61, U$12.61
GP130_UART_1_RX6: U$13.61, U$14.61
GP130_UART_1_RX7: U$15.61, U$16.61
GP131_UART_1_TX: U$2.46, U$3.46
GP131_UART_1_TX1: U$1.46, U$4.46
GP131_UART_1_TX2: U$5.46, U$6.46
GP131_UART_1_TX3: U$7.46, U$8.46
GP131_UART_1_TX4: U$9.46, U$10.46
GP131_UART_1_TX5: U$11.46, U$12.46
GP131_UART_1_TX6: U$13.46, U$14.46
GP131_UART_1_TX7: U$15.46, U$16.46
GP134_UART_2_RX: U$2.22, U$3.22
GP134_UART_2_RX1: U$1.22, U$4.22
GP134_UART_2_RX2: U$5.22, U$6.22
GP134_UART_2_RX3: U$7.22, U$8.22
GP134_UART_2_RX4: U$9.22, U$10.22
GP134_UART_2_RX5: U$11.22, U$12.22
GP134_UART_2_RX6: U$13.22, U$14.22
GP134_UART_2_RX7: U$15.22, U$16.22
GP135_UART_2_TX: U$2.27, U$3.27
GP135_UART_2_TX1: U$1.27, U$4.27
GP135_UART_2_TX2: U$5.27, U$6.27
GP135_UART_2_TX3: U$7.27, U$8.27
GP135_UART_2_TX4: U$9.27, U$10.27
GP135_UART_2_TX5: U$11.27, U$12.27
GP135_UART_2_TX6: U$13.27, U$14.27
GP135_UART_2_TX7: U$15.27, U$16.27
GP165: U$2.25, U$3.25
GP182_PWM1: U$1.37, U$4.37
GP182_PWM2: U$2.37, U$3.37
GP182_PWM3: U$5.37, U$6.37
GP182_PWM4: U$7.37, U$8.37
GP182_PWM5: U$9.37, U$10.37
GP182_PWM6: U$11.37, U$12.37
GP182_PWM7: U$13.37, U$14.37
GP182_PWM8: U$15.37, U$16.37
GP183_PWM1: U$1.39, U$4.39
GP183_PWM2: U$5.39, U$6.39
GP183_PWM3: U$2.39, U$3.39
GP183_PWM4: U$7.39, U$8.39
GP183_PWM5: U$9.39, U$10.39
GP183_PWM6: U$11.39, U$12.39
GP183_PWM7: U$13.39, U$14.39
GP183_PWM8: U$15.39, U$16.39
HV_SCL: JP2.1, R2.1, U2.6
HV_SCL1: JP1.1, R7.1, U3.6
HV_SCL2: JP3.1, R12.1, U5.6
HV_SCL3: JP4.1, R17.1, U7.6
HV_SCL4: JP5.1, R22.1, U9.6
HV_SCL5: JP6.1, R27.1, U11.6
HV_SCL6: JP7.1, R32.1, U13.6
HV_SCL7: JP8.1, R37.1, U15.6
HV_SDA: JP2.2, R1.1, U2.5
HV_SDA1: JP1.2, R6.1, U3.5
HV_SDA2: JP3.2, R11.1, U5.5
HV_SDA3: JP4.2, R16.1, U7.5
HV_SDA4: JP5.2, R21.1, U9.5
HV_SDA5: JP6.2, R26.1, U11.5
HV_SDA6: JP7.2, R31.1, U13.5
HV_SDA7: JP8.2, R36.1, U15.5
MSIC_SLP_CLK: U$2.7, U$3.7
MSIC_SLP_CLK1: U$1.7, U$4.7
MSIC_SLP_CLK2: U$5.7, U$6.7
MSIC_SLP_CLK3: U$7.7, U$8.7
MSIC_SLP_CLK4: U$9.7, U$10.7
MSIC_SLP_CLK5: U$11.7, U$12.7
MSIC_SLP_CLK6: U$13.7, U$14.7
MSIC_SLP_CLK7: U$15.7, U$16.7
unnamed: R3.1, U2.7, U2.8
unnamed: R8.1, U3.7, U3.8
unnamed: R13.1, U5.7, U5.8
unnamed: R18.1, U7.7, U7.8
unnamed: R23.1, U9.7, U9.8
unnamed: R28.1, U11.7, U11.8
unnamed: R33.1, U13.7, U13.8
unnamed: R38.1, U15.7, U15.8
OSC_CLK_OUT: U$2.67, U$3.67
OSC_CLK_OUT1: U$1.67, U$4.67
OSC_CLK_OUT2: U$5.67, U$6.67
OSC_CLK_OUT3: U$7.67, U$8.67
OSC_CLK_OUT4: U$9.67, U$10.67
OSC_CLK_OUT5: U$11.67, U$12.67
OSC_CLK_OUT6: U$13.67, U$14.67
OSC_CLK_OUT7: U$15.67, U$16.67
PSW: U$2.21, U$3.21
PSW1: U$1.21, U$4.21
PSW2: U$5.21, U$6.21
PSW3: U$7.21, U$8.21
PSW4: U$9.21, U$10.21
PSW5: U$11.21, U$12.21
PSW6: U$13.21, U$14.21
PSW7: U$15.21, U$16.21
PWRBTN#: U$2.17, U$3.17
PWRBTN#1: U$1.17, U$4.17
PWRBTN#2: U$5.17, U$6.17
PWRBTN#3: U$7.17, U$8.17
PWRBTN#4: U$9.17, U$10.17
PWRBTN#5: U$11.17, U$12.17
PWRBTN#6: U$13.17, U$14.17
PWRBTN#7: U$15.17, U$16.17
RCVR_MODE: U$2.31, U$3.31
RCVR_MODE1: U$1.31, U$4.31
RCVR_MODE2: U$5.31, U$6.31
RCVR_MODE3: U$7.31, U$8.31
RCVR_MODE4: U$9.31, U$10.31
RCVR_MODE5: U$11.31, U$12.31
RCVR_MODE6: U$13.31, U$14.31
RCVR_MODE7: U$15.31, U$16.31
RESET_OUT#: U$2.36, U$3.36
RESET_OUT#1: U$1.36, U$4.36
RESET_OUT#2: U$5.36, U$6.36
RESET_OUT#3: U$7.36, U$8.36
RESET_OUT#4: U$9.36, U$10.36
RESET_OUT#5: U$11.36, U$12.36
RESET_OUT#6: U$13.36, U$14.36
RESET_OUT#7: U$15.36, U$16.36
USB_DN: U$2.18, U$3.18
USB_DN1: U$1.18, U$4.18
USB_DN2: U$5.18, U$6.18
USB_DN3: U$7.18, U$8.18
USB_DN4: U$9.18, U$10.18
USB_DN5: U$11.18, U$12.18
USB_DN6: U$13.18, U$14.18
USB_DN7: U$15.18, U$16.18
USB_DP: U$2.16, U$3.16
USB_DP1: U$1.16, U$4.16
USB_DP2: U$5.16, U$6.16
USB_DP3: U$7.16, U$8.16
USB_DP4: U$9.16, U$10.16
USB_DP5: U$11.16, U$12.16
USB_DP6: U$13.16, U$14.16
USB_DP7: U$15.16, U$16.16
USB_ID: U$2.3, U$3.3
USB_ID1: U$1.3, U$4.3
USB_ID2: U$5.3, U$6.3
USB_ID3: U$7.3, U$8.3
USB_ID4: U$9.3, U$10.3
USB_ID5: U$11.3, U$12.3
USB_ID6: U$13.3, U$14.3
USB_ID7: U$15.3, U$16.3
USB_VBUS: U$2.20, U$3.20
USB_VBUS1: U$1.20, U$4.20
USB_VBUS2: U$5.20, U$6.20
USB_VBUS3: U$7.20, U$8.20
USB_VBUS4: U$9.20, U$10.20
USB_VBUS5: U$11.20, U$12.20
USB_VBUS6: U$13.20, U$14.20
USB_VBUS7: U$15.20, U$16.20
VOUT: C2.1, JP2.3, R1.2, R2.2, R3.2, SJ1.2
VOUT1: C6.1, JP1.3, R6.2, R7.2, R8.2, SJ2.2
VOUT2: C10.1, JP3.3, R11.2, R12.2, R13.2, SJ3.2
VOUT3: C14.1, JP4.3, R16.2, R17.2, R18.2, SJ4.2
VOUT4: C18.1, JP5.3, R21.2, R22.2, R23.2, SJ5.2
VOUT5: C22.1, JP6.3, R26.2, R27.2, R28.2, SJ6.2
VOUT6: C26.1, JP7.3, R31.2, R32.2, R33.2, SJ7.2
VOUT7: C30.1, JP8.3, R36.2, R37.2, R38.2, SJ8.2
VSYS: C3.1, SJ1.1, U1.1, U1.3, U$2.2, U$2.4, U$2.6, U$3.2, U$3.4, U$3.6
VSYS1: C7.1, SJ2.1, U4.1, U4.3, U$1.2, U$1.4, U$1.6, U$4.2, U$4.4, U$4.6
VSYS2: C11.1, SJ3.1, U6.1, U6.3, U$5.2, U$5.4, U$5.6, U$6.2, U$6.4, U$6.6
VSYS3: C15.1, SJ4.1, U8.1, U8.3, U$7.2, U$7.4, U$7.6, U$8.2, U$8.4, U$8.6
VSYS4: C19.1, SJ5.1, U10.1, U10.3, U$9.2, U$9.4, U$9.6, U$10.2, U$10.4, U$10.6
VSYS5: C23.1, SJ6.1, U12.1, U12.3, U$11.2, U$11.4, U$11.6, U$12.2, U$12.4, U$12.6
VSYS6: C27.1, SJ7.1, U14.1, U14.3, U$13.2, U$13.4, U$13.6, U$14.2, U$14.4, U$14.6
VSYS7: C31.1, SJ8.1, U16.1, U16.3, U$15.2, U$15.4, U$15.6, U$16.2, U$16.4, U$16.6
V_BAT_BKUP: U$2.23, U$3.23
V_BAT_BKUP1: U$1.23, U$4.23
V_BAT_BKUP2: U$5.23, U$6.23
V_BAT_BKUP3: U$7.23, U$8.23
V_BAT_BKUP4: U$9.23, U$10.23
V_BAT_BKUP5: U$11.23, U$12.23
V_BAT_BKUP6: U$13.23, U$14.23
V_BAT_BKUP7: U$15.23, U$16.23

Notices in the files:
parts and their libraries:
SparkFun-Aesthetics: Licensing: Creative Commons ShareAlike 4.0 International - https://creativecommons.org/licenses/by-sa/4.0
SparkFun-Aesthetics: Released under the Creative Commons Attribution Share-Alike 4.0 License
SparkFun-Aesthetics: Released under the Creative Commons
